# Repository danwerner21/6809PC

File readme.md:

# 6809PC
The 6809PC is a 6809 ATX format board with 512K RAM, 4K ROM, with a flexible programmable MMU, battery backed up RTC, 6551 UART, and 6 ISAish slots.  This computer will run the fantastic CUBIX operating system by Dave Dunfield.  

See this repo (https://github.com/danwerner21/CUBIX09) for ROM image and operating system.

## BUGS
I have not built the 1.31 version, but it contains fixes for the only bug found in the 1.30 version which was in the ATX power switch circuit. The ICs in that circuit were not powered by standby power, they were powered by +5 which made them non-functional.  There are no known remaining bugs in the 1.31 board.

### Jumper Settings
J1,J2,J5,J7,J9,J13 - ISA SLOT IRQ Selection
J11 - TTL Serial Port Connection
J12 - TTL Console Power

K1 - ROM BANK Selection (2-3 high bank, 1-2 Low Bank)
K2 - MMU Selection (1-2 Disable on int, 3-4 Clear Task register on int)

JP1 - Reset Swithc Connection
JP3 - CTS Pull Up Enable

P12 - Power Switch Connection
P15 - CPU Speed Selection
P18 - Serial Port Connection

### Building the system

### Default Memory Map
            $0000-$E000 - RAM
            $E000-$EFFF - Memory Mapped IO
            $F000-$FFFF - ROM

### Bill Of Materials
Reference|Value|Qty|Field1|Description
---------|-----|---|------|-----------
C1-C4,C17|22 uF|5||Polarized capacitor
C5-C16,C18-C27,C29-C33,C36-C54,C56,C58,C62|0.1 uF|49||Unpolarized capacitor
C28|1uF|1||Polarized capacitor
C35|10uF|1||Polarized capacitor
C57|0.01 uF|1||Unpolarized capacitor
C59,C60|15pf|2||Unpolarized capacitor
C61,C63-C66|1.0 uF|5||Polarized capacitor
D1,D2|1N4148|2||Diode
D3,D4|D|2||Diode
J1,J2,J5,J7,J9,J13|IRQ Selection|6||Generic connector, double row, 02x06, odd/even pin numbering scheme (row 1 odd numbers, row 2 even numbers), script generated (kicad-library-utils/schlib/autogen/connector/)
J3,J4,J6,J8,J10,J14|Bus_ISA_8bit|6||8-bit ISA-PC bus connector
J11|TTL SERIAL CONSOLE|1||Generic connector, single row, 01x06, script generated (kicad-library-utils/schlib/autogen/connector/)
J12|TTL CONSOLE PWR|1||Generic connector, single row, 01x02, script generated (kicad-library-utils/schlib/autogen/connector/)
JP1,JP3|JUMPER|2||-- mixed values --
K1|ROM SELECT|1||Generic connector, single row, 01x03, script generated (kicad-library-utils/schlib/autogen/connector/)
K2|MMU-INTA|1||Generic connector, single row, 01x03, script generated (kicad-library-utils/schlib/autogen/connector/)
P1|SHADOW ADDR|1||Generic connector, double row, 02x04, odd/even pin numbering scheme (row 1 odd numbers, row 2 even numbers), script generated (kicad-library-utils/schlib/autogen/connector/)
P11|CONN_10X2|1||Generic connector, double row, 02x10, odd/even pin numbering scheme (row 1 odd numbers, row 2 even numbers), script generated (kicad-library-utils/schlib/autogen/connector/)
P12|POWER_SW|1||Generic connector, single row, 01x02, script generated (kicad-library-utils/schlib/autogen/connector/)
P13|14.31818 MHz CLK|1||
P14|16.000Mhz|1||
P15|CPU CLOCK SPEED|1||Generic connector, double row, 02x04, odd/even pin numbering scheme (row 1 odd numbers, row 2 even numbers), script generated (kicad-library-utils/schlib/autogen/connector/)
P16|CONN_4|1||Generic connector, single row, 01x04, script generated (kicad-library-utils/schlib/autogen/connector/)
P17|1.8432 MHz CLK|1||
P18|SERIAL|1||Generic connector, double row, 02x05, odd/even pin numbering scheme (row 1 odd numbers, row 2 even numbers), script generated (kicad-library-utils/schlib/autogen/connector/)
R1,R3|10k|2||Resistor
R2|470|1||Resistor
R4,R7,R26|4.7K|3||Resistor
R5,R6,R8|1000|3||Resistor
RR1|2200|1||9 resistor network, star topology, bussed resistors, small symbol
RR2|22K|1||9 resistor network, star topology, bussed resistors, small symbol
SW1|POWER|1||Push button switch, generic, two pins
SW2|RESET|1||Push button switch, generic, two pins
U1|74LS04|1||Hex Inverter
U2,U34,U36,U39,U45,U46|74LS244|6||Octal Buffer and Line Driver With 3-State Output, active-low enables, non-inverting outputs
U3|74LS682|1||
U4|74LS86|1||Quad 2-input XOR
U5|74LS02|1||quad 2-input NOR gate
U6,U21|74LS00|2||quad 2-input NAND gate
U7,U10,U16|74LS32|3||Quad 2-input OR
U8|SRAM_512K|1||512K x 8 Low Power CMOS RAM, DIP-32
U9,U15|74LS08|2||Quad And2
U11|27C256|1||OTP EPROM 256 KiBit
U12,U22|74LS74|2||Dual D Flip-flop, Set & Reset
U17|74LS14|1||Hex inverter schmitt trigger
U18|74LS06|1||Inverter Open Collect
U19|74HCT14|1||Hex inverter schmitt trigger
U23|74LS688|1||8-bit magnitude comparator
U24,U42|74LS138|2||Decoder 3 to 8 active low outputs
U25-U28,U32,U41|74LS245|6||Octal BUS Transceivers, 3-State outputs
U29|DS1233|1||
U30|74LS163|1||Synchronous 4-bit programmable binary Counter
U31|74LS240|1||Octal Buffer and Line Driver With 3-State Output, active-low enables, inverting outputs
U33|MC68B09|1||8-Bit Microprocessing unit 2.0MHz, DIP-40
U35|74LS174|1||Hex D-type Flip-Flop, reset
U37|74LS157|1||Quad 2 to 1 line Multiplexer
U38|74LS374|1||8-bit Register, 3-state outputs
U40|SRAM-32K|1||256K (32K x 8) Static RAM, 70ns, DIP-28
U43,U44|74LS257|2||Quad 2 to 1 Multiplexer
U47|M6242|1||M6242
U48|G65SC51P|1||CMOS Asynchronous Communication Interface Adapter (ACIA), Serial UART, DIP-28
U49|MAX232|1||Dual RS232 driver/receiver, 5V supply, 120kb/s, 0C-70C
X1|RTC_OSC|1|32.768 KHz|Two pin crystal

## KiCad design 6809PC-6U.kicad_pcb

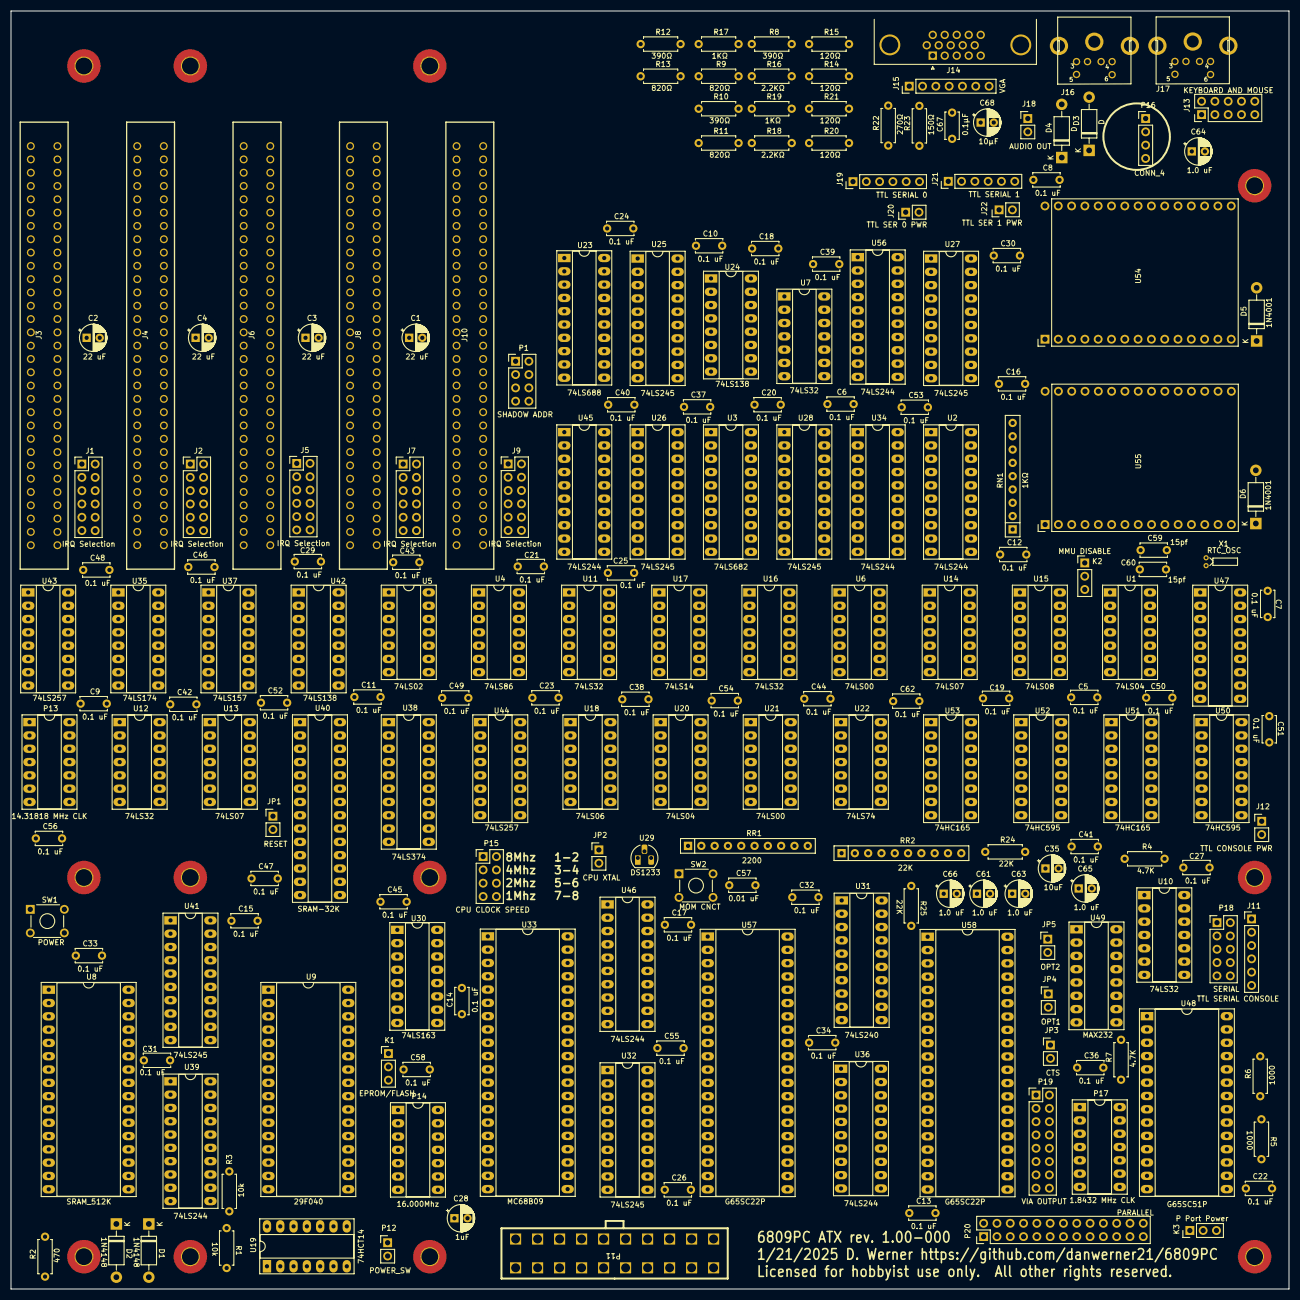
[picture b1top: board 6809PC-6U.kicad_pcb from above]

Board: 2 copper layers, 244.0 x 244.0 mm, 216 parts (0 on the bottom side), 371 nets, no tracks yet.

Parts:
C1, C2, C3, C4: 22 uF; STD_DDW_PCAP
C5, C6, C7, C8, C9, C10, C11, C12, C13, C14, C15, C16, C17, C18, C19, C20, C21, C22, C23, C24, C25, C26, C27, C29, C30, C31, C32, C33, C34, C36, C37, C38, C39, C40, C41, C42, C43, C44, C45, C46, C47, C48, C49, C50, C51, C52, C53, C54, C55, C56, C58, C62: 0.1 uF; STD_DDW_CAP
C28: 1uF; STD_DDW_PCAP
C35: 10uF; STD_DDW_PCAP
C57: 0.01 uF; STD_DDW_CAP
C59, C60: 15pf; STD_DDW_CAP
C61, C63, C64, C65, C66: 1.0 uF; STD_DDW_PCAP
C67: 0.1µF; STD_DDW_CAP
C68: 10µF; STD_DDW_PCAP
D1, D2: 1N4148; STD_DDW_DIODE
D3, D4: D; STD_DDW_DIODE
D5, D6: 1N4001; STD_DDW_DIODE
J1, J2, J5, J7, J9: IRQ Selection; STD_DDW_PINHEAD_V_2x06
J3, J4, J6, J8, J10: Bus_ISA_8bit; BUSPC_HOST
J11: TTL SERIAL CONSOLE; STD_DDW_PINHEAD_V_1x06
J12: TTL CONSOLE PWR; STD_DDW_PINHEAD_V_1x02
J13: KEYBOARD AND MOUSE; STD_DDW_PINHEAD_V_2x05
J14: VGA; STD_DDW_VGA
J15: VGA; STD_DDW_PINHEAD_V_1x07
J16: Keyboard; PS2_DIN
J17: Mouse; PS2_DIN
J18: AUDIO OUT; STD_DDW_PINHEAD_V_1x02
J19: TTL SERIAL 0; STD_DDW_PINHEAD_V_1x06
J20: TTL SER 0 PWR; STD_DDW_PINHEAD_V_1x02
J21: TTL SERIAL 1; STD_DDW_PINHEAD_V_1x06
J22: TTL SER 1 PWR; STD_DDW_PINHEAD_V_1x02
JP1: RESET; STD_DDW_PINHEAD_V_1x02
JP2: CPU XTAL; STD_DDW_PINHEAD_V_1x02
JP3: CTS; STD_DDW_PINHEAD_V_1x02
JP4: OPT1; STD_DDW_PINHEAD_V_1x02
JP5: OPT2; STD_DDW_PINHEAD_V_1x02
K1: EPROM/FLASH; STD_DDW_PINHEAD_V_1x03
K2: MMU DISABLE; STD_DDW_PINHEAD_V_1x03
K3: P Port Power; STD_DDW_PINHEAD_V_1x03
P1: SHADOW ADDR; STD_DDW_PINHEAD_V_2x04
P2, P3, P4, P5, P6, P7, P8, P9, P10, P21, P22, P23: CONN_1; MountingHole_3.2mm_M3_Pad_TopBottom
P11: CONN_10X2; ATXConnector
P12: POWER_SW; STD_DDW_PINHEAD_V_1x02
P13: 14.31818 MHz CLK; STD_DDW_DIP14
P14: 16.000Mhz; STD_DDW_DIP14
P15: CPU CLOCK SPEED; STD_DDW_PINHEAD_V_2x04
P16: CONN_4; STD_DDW_PINHEAD_V_1x04
P17: 1.8432 MHz CLK; STD_DDW_DIP14
P18: SERIAL; STD_DDW_PINHEAD_V_2x05
P19: VIA OUTPUT; STD_DDW_PINHEAD_V_2x08
P20: PARALLEL; STD_DDW_PINHEAD_V_2x13
R1, R3: 10k; STD_DDW_RESISTOR
R2: 470; STD_DDW_RESISTOR
R4, R7: 4.7K; STD_DDW_RESISTOR
R5, R6: 1000; STD_DDW_RESISTOR
R8, R10, R12: 390Ω; STD_DDW_RESISTOR
R9, R11, R13: 820Ω; STD_DDW_RESISTOR
R14, R15, R20, R21: 120Ω; STD_DDW_RESISTOR
R16, R18: 2.2KΩ; STD_DDW_RESISTOR
R17, R19: 1KΩ; STD_DDW_RESISTOR
R22: 270Ω; STD_DDW_RESISTOR
R23: 150Ω; STD_DDW_RESISTOR
R24, R25: 22K; STD_DDW_RESISTOR
RN1: 1KΩ; STD_DDW_SIP9
RR1: 2200; STD_DDW_SIP10
RR2: 22K; STD_DDW_SIP10
SW1: POWER; STD_DDW_TACTSW
SW2: MOM CNCT; STD_DDW_TACTSW
U1, U20: 74LS04; STD_DDW_DIP14
U2, U34, U36, U39, U45, U46, U56: 74LS244; STD_DDW_DIP20
U3: 74LS682; STD_DDW_DIP20
U4: 74LS86; STD_DDW_DIP14
U5: 74LS02; STD_DDW_DIP14
U6, U21: 74LS00; STD_DDW_DIP14
U7, U10, U11, U12, U16: 74LS32; STD_DDW_DIP14
U8: SRAM_512K; STD_DDW_DIP32
U9: 29F040; STD_DDW_DIP32
U13, U14: 74LS07; STD_DDW_DIP14
U15: 74LS08; STD_DDW_DIP14
U17: 74LS14; STD_DDW_DIP14
U18: 74LS06; STD_DDW_DIP14
U19: 74HCT14; STD_DDW_DIP14
U22: 74LS74; STD_DDW_DIP14
U23: 74LS688; STD_DDW_DIP20
U24, U42: 74LS138; STD_DDW_DIP16
U25, U26, U27, U28, U32, U41: 74LS245; STD_DDW_DIP20
U29: DS1233; STD_DDW_TO92
U30: 74LS163; STD_DDW_DIP16
U31: 74LS240; STD_DDW_DIP20
U33: MC68B09; STD_DDW_DIP40
U35: 74LS174; STD_DDW_DIP16
U37: 74LS157; STD_DDW_DIP16
U38: 74LS374; STD_DDW_DIP20
U40: SRAM-32K; STD_DDW_DIP28_SKINNY
U43, U44: 74LS257; STD_DDW_DIP16
U47: STD_DDW_DIP18
U48: G65SC51P; STD_DDW_DIP28
U49: MAX232; STD_DDW_DIP16
U50, U52: 74HC595; STD_DDW_DIP16
U51, U53: 74HC165; STD_DDW_DIP16
U54, U55: ESP32_MODULE; ESP32_Module
U57, U58: G65SC22P; STD_DDW_DIP40
X1: RTC_OSC; DDW_STD_RTCCRYSTAL

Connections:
5VSB: D1.1 (K), D2.1 (K), P11.17, R1.1, R3.2, U19.9, U19.11, U19.13, U22.1 (~R)
+3V3: C8.1, C12.1, C16.1, C20.1, C24.1, P11.1, P11.2, P11.3, R16.2, R17.2, R18.2, R19.2, RN1.1 (common)
+12V: J3.9 (+12V), J4.9 (+12V), J6.9 (+12V), J8.9 (+12V), J10.9 (+12V), P11.19
-5V: J3.5 (-5V), J4.5 (-5V), J6.5 (-5V), J8.5 (-5V), J10.5 (-5V), P11.16
-12V: J3.7 (-12V), J4.7 (-12V), J6.7 (-12V), J8.7 (-12V), J10.7 (-12V), P11.4
/ACIA/ACIA_CLK: P17.8, P17.9, P17.10, P17.11, U48.6 (XTAL1)
/ACIA/CTS: JP3.2 (B), P18.6, U49.13 (R1IN)
/ACIA/CTS_TTL: U48.9 (~CTS), U49.12 (R1OUT)
/ACIA/DCD: R6.2, U48.16 (~DCD)
/ACIA/DSR: R5.2, U48.17 (~DSR)
/ACIA/DTR: R7.2, U48.11 (~DTR)
/ACIA/RTS: P18.4, U49.14 (T1OUT)
/ACIA/RTS_TTL: U48.8 (~RTS), U49.11 (T1IN)
/ACIA/RXD: P18.3, U49.8 (R2IN)
/ACIA/RXD_TTL: J11.4, U48.12 (RxD), U49.9 (R2OUT)
/ACIA/TXD: P18.5, U49.7 (T2OUT)
/ACIA/TXD_TTL: J11.5, U48.10 (TxD), U49.10 (T2IN)
/CPU 6809/1MHZ: P15.7, U30.11 (Q3)
/CPU 6809/2MHZ: P15.5, U30.12 (Q2)
/CPU 6809/4MHZ: P15.3, U30.13 (Q1)
/CPU 6809/8MHZ: P15.1, U30.14 (Q0)
/CPU 6809//INTA: K2.2, U21.3
/MMU four/MMU-ENABLE: U22.9 (Q), U36.2 (I0a), U37.1 (S), U43.1 (S), U44.1 (S)
/MMU four//MMU-ENB-WR: U22.11 (C), U42.13 (O2)
/MMU four//MMU-MAP-RD: U10.11, U15.1
/MMU four//MMU-MAP-WR: U10.8, U40.27 (~WE)
/MMU four//MMU-TASK-RD: U36.1 (OEa), U36.4 (I1a), U36.19 (OEb), U42.11 (O4)
/MMU four//MMU-TASK-SETUP-WR: U38.11 (Cp), U42.14 (O1)
/MMU four//MMU-TASK-WR: U35.9 (Cp), U42.15 (O0)
/MMU four//OE: U15.3, U40.22 (~OE)
/Memory Map/SHADOW-ROM: U5.10, U5.11
/Memory Map//SHADOW: U3.19 (~P=Q), U5.5, U5.9, U6.2
/VIAS/CA1: P19.3, U57.40 (CA1)
/VIAS/CA2: P19.5, U57.39 (CA2)
/VIAS/CB1: P19.7, U57.18 (CB1)
/VIAS/CB2: P19.9, U57.19 (CB2)
/VIAS/CC1: P19.11, U58.40 (CA1)
/VIAS/CC2: P19.13, U58.39 (CA2)
/VIAS/PA0: P20.2, U57.2 (PA0)
/VIAS/PA1: P20.4, U57.3 (PA1)
/VIAS/PA2: P20.6, U57.4 (PA2)
/VIAS/PA3: P20.8, U57.5 (PA3)
/VIAS/PA4: P20.10, U57.6 (PA4)
/VIAS/PA5: P20.12, U57.7 (PA5)
/VIAS/PA6: P20.14, U57.8 (PA6)
/VIAS/PA7: P20.16, U57.9 (PA7)
/VIAS/PB0: P20.18, U57.10 (PB0)
/VIAS/PB1: P20.20, U57.11 (PB1)
/VIAS/PB2: P20.22, U57.12 (PB2)
/VIAS/PB3: P20.24, U57.13 (PB3)
/VIAS/PB4: P20.23, U57.14 (PB4)
/VIAS/PB5: P20.21, U57.15 (PB5)
/VIAS/PB6: P20.19, U57.16 (PB6)
/VIAS/PB7: P20.17, U57.17 (PB7)
/VIAS/PC0: P20.1, U58.2 (PA0)
/VIAS/PC1: P20.3, U58.3 (PA1)
/VIAS/PC2: P20.5, U58.4 (PA2)
/VIAS/PC3: P20.7, U58.5 (PA3)
/VIAS/PC4: P20.9, U58.6 (PA4)
/VIAS/PC5: P20.11, U58.7 (PA5)
/VIAS/PC6: P20.13, U58.8 (PA6)
/VIAS/PC7: P20.15, U58.9 (PA7)
/VIAS/PPWR: K3.2, P20.25
AUDIO: R22.1, U54.8 (GPIO25)
BUSAK: U4.9, U17.4, U32.19 (CE), U34.1 (OEa), U43.15 (OE), U44.15 (OE), U45.19 (OEb), U46.1 (OEa), U46.19 (OEb)
BUSALE: J3.28 (ALE), J4.28 (ALE), J6.28 (ALE), J8.28 (ALE), J10.28 (ALE), U17.2, U47.3 (ALE)
BUSCLK: J3.30 (OSC), J4.30 (OSC), J6.30 (OSC), J8.30 (OSC), J10.30 (OSC), P13.8, P13.9, P13.10, P13.11
B_A0: J3.62 (BA00), J4.62 (BA00), J6.62 (BA00), J8.62 (BA00), J10.62 (BA00), U26.18 (B0)
B_A1: J3.61 (BA01), J4.61 (BA01), J6.61 (BA01), J8.61 (BA01), J10.61 (BA01), U26.17 (B1)
B_A2: J3.60 (BA02), J4.60 (BA02), J6.60 (BA02), J8.60 (BA02), J10.60 (BA02), U26.16 (B2)
B_A3: J3.59 (BA03), J4.59 (BA03), J6.59 (BA03), J8.59 (BA03), J10.59 (BA03), U26.15 (B3)
B_A4: J3.58 (BA04), J4.58 (BA04), J6.58 (BA04), J8.58 (BA04), J10.58 (BA04), U26.14 (B4)
B_A5: J3.57 (BA05), J4.57 (BA05), J6.57 (BA05), J8.57 (BA05), J10.57 (BA05), U26.13 (B5)
B_A6: J3.56 (BA06), J4.56 (BA06), J6.56 (BA06), J8.56 (BA06), J10.56 (BA06), U26.12 (B6)
B_A7: J3.55 (BA07), J4.55 (BA07), J6.55 (BA07), J8.55 (BA07), J10.55 (BA07), U26.11 (B7)
B_A8: J3.54 (BA08), J4.54 (BA08), J6.54 (BA08), J8.54 (BA08), J10.54 (BA08), U27.18 (B0)
B_A9: J3.53 (BA09), J4.53 (BA09), J6.53 (BA09), J8.53 (BA09), J10.53 (BA09), U27.17 (B1)
B_A10: J3.52 (BA10), J4.52 (BA10), J6.52 (BA10), J8.52 (BA10), J10.52 (BA10), U27.16 (B2)
B_A11: J3.51 (BA11), J4.51 (BA11), J6.51 (BA11), J8.51 (BA11), J10.51 (BA11), U27.15 (B3)
B_A12: J3.50 (BA12), J4.50 (BA12), J6.50 (BA12), J8.50 (BA12), J10.50 (BA12), U27.14 (B4)
B_A13: J3.49 (BA13), J4.49 (BA13), J6.49 (BA13), J8.49 (BA13), J10.49 (BA13), U27.13 (B5)
B_A14: J3.48 (BA14), J4.48 (BA14), J6.48 (BA14), J8.48 (BA14), J10.48 (BA14), U27.12 (B6)
B_A15: J3.47 (BA15), J4.47 (BA15), J6.47 (BA15), J8.47 (BA15), J10.47 (BA15), U27.11 (B7)
B_A16: J3.46 (BA16), J4.46 (BA16), J6.46 (BA16), J8.46 (BA16), J10.46 (BA16), U28.18 (B0)
B_A17: J3.45 (BA17), J4.45 (BA17), J6.45 (BA17), J8.45 (BA17), J10.45 (BA17), U28.17 (B1)
B_A18: J3.44 (BA18), J4.44 (BA18), J6.44 (BA18), J8.44 (BA18), J10.44 (BA18), U28.16 (B2)
B_A19: J3.43 (BA19), J4.43 (BA19), J6.43 (BA19), J8.43 (BA19), J10.43 (BA19), U28.15 (B3)
B_D0: J3.40 (DB0), J4.40 (DB0), J6.40 (DB0), J8.40 (DB0), J10.40 (DB0), U25.18 (B0)
B_D1: J3.39 (DB1), J4.39 (DB1), J6.39 (DB1), J8.39 (DB1), J10.39 (DB1), U25.17 (B1)
B_D2: J3.38 (DB2), J4.38 (DB2), J6.38 (DB2), J8.38 (DB2), J10.38 (DB2), U25.16 (B2)
B_D3: J3.37 (DB3), J4.37 (DB3), J6.37 (DB3), J8.37 (DB3), J10.37 (DB3), U25.15 (B3)
B_D4: J3.36 (DB4), J4.36 (DB4), J6.36 (DB4), J8.36 (DB4), J10.36 (DB4), U25.14 (B4)
B_D5: J3.35 (DB5), J4.35 (DB5), J6.35 (DB5), J8.35 (DB5), J10.35 (DB5), U25.13 (B5)
B_D6: J3.34 (DB6), J4.34 (DB6), J6.34 (DB6), J8.34 (DB6), J10.34 (DB6), U25.12 (B6)
B_D7: J3.33 (DB7), J4.33 (DB7), J6.33 (DB7), J8.33 (DB7), J10.33 (DB7), U25.11 (B7)
B_INT: J1.1, J1.2, J1.3, J1.4, J1.5, J1.6, J2.1, J2.2, J2.3, J2.4, J2.5, J2.6, J5.1, J5.2, J5.3, J5.4, J5.5, J5.6, J7.1, J7.2, J7.3, J7.4, J7.5, J7.6, J9.1, J9.2, J9.3, J9.4, J9.5, J9.6, U18.13
B_/CLK: J3.20 (CLK), J4.20 (CLK), J6.20 (CLK), J8.20 (CLK), J10.20 (CLK), U31.18 (O0a)
B_/INT: RR1.2 (R1), U18.12, U31.6 (I2a)
B_/IORQ: U7.12, U16.4, U34.5 (O2b)
B_/MREQ: U16.1, U16.9, U28.12 (B6)
B_/NMI: J3.32 (IO), J4.32 (IO), J6.32 (IO), J8.32 (IO), J10.32 (IO), RR1.9 (R8), U31.4 (I1a)
B_/RD: U16.5, U16.10, U28.14 (B4)
B_/WR: U7.13, U16.2, U28.13 (B5)
CD1: JP4.2 (B), R24.2, U58.18 (CB1)
CD2: JP5.2 (B), R25.2, U58.19 (CB2)
CLK: P15.2, P15.4, P15.6, P15.8, U31.2 (I0a), U33.38 (EXTAL)
CPU_BA: U1.11, U33.6 (BA)
CPU_BS: RR2.10 (R9), U21.2, U33.5 (BS)
CPU_D0: U32.18 (B0), U33.31 (D0)
CPU_D1: U32.17 (B1), U33.30 (D1)
CPU_D2: U32.16 (B2), U33.29 (D2)
CPU_D3: U32.15 (B3), U33.28 (D3)
CPU_D4: U32.14 (B4), U33.27 (D4)
CPU_D5: U32.13 (B5), U33.26 (D5)
CPU_D6: U32.12 (B6), U33.25 (D6)
CPU_D7: U32.11 (B7), U33.24 (D7)
CPU_E: U5.2, U6.10, U33.34 (E), U34.17 (I3b), U45.6 (I2a)
CPU_Q: U5.3, U17.1, U33.35 (Q), U45.4 (I1a)
CPU_R/W: U1.1, U6.5, U33.32 (R/~W), U34.8 (I3a), U45.8 (I3a)
CPU_/RD: U6.6, U10.13, U12.10, U12.13, U16.13, U34.4 (I1a), U47.8 (RD)
CPU_/WR: U6.8, U10.9, U12.2, U12.5, U34.6 (I2a), U47.10 (WR)
E: U6.4, U34.3 (O3b), U42.6 (E3), U45.14 (O2a), U48.27 (ϕ2), U57.25 (ϕ2), U58.25 (ϕ2)
ESP0_BUSY: U54.11 (GPIO14), U56.4 (I1a)
ESP0_IN: RN1.7 (R6), U14.12, U54.22 (GPIO17)
ESP0_INCLK: U53.2 (CP), U54.10 (GPIO27)
ESP0_OUT: U52.14 (SER), U54.21 (GPIO16)
ESP0_OUTCLK: U52.11 (SRCLK), U52.12 (RCLK), U54.9 (GPIO26)
ESP0_RDYO: U54.12 (GPIO12), U56.2 (I0a)
ESP0_SEL: U11.6, U12.1, U12.9
ESP0_SPAREO: U54.19 (GPIO2), U56.6 (I2a)
ESP1_BUSY: U55.24 (GPIO18), U56.11 (I0b)
ESP1_IN: RN1.2 (R1), U14.10, U55.22 (GPIO17)
ESP1_INCLK: U51.2 (CP), U55.25 (GPIO19)
ESP1_OUT: U50.14 (SER), U55.21 (GPIO16)
ESP1_OUTCLK: U50.11 (SRCLK), U50.12 (RCLK), U55.26 (GPIO21)
ESP1_RDYO: U55.23 (GPIO5), U56.8 (I3a)
ESP1_SEL: U11.8, U12.4, U12.12
ESPSTAT_SEL: U11.11, U16.12
GND: C1.2, C2.2, C3.2, C4.2, C5.2, C6.2, C7.2, C8.2, C9.2, C10.2, C11.2, C12.2, C13.2, C14.2, C15.2, C16.2, C17.2, C18.2, C19.2, C20.2, C21.2, C22.2, C23.2, C24.2, C25.2, C26.2, C27.2, C28.2, C29.2, C30.2, C31.2, C32.2, C33.2, C34.2, C35.2, C36.2, C37.2, C38.2, C39.2, C40.2, C41.2, C42.2, C43.2, C44.2, C45.2, C46.2, C47.2, C48.2, C49.2, C50.2, C51.2, C52.2, C53.2, C54.2, C55.2, C56.2, C57.2, C58.2, C62.2, C64.2, C65.1, C67.2, J3.1 (GND), J3.10 (GND), J3.31 (GND), J4.1 (GND), J4.10 (GND), J4.31 (GND), J6.1 (GND), J6.10 (GND), J6.31 (GND), J8.1 (GND), J8.10 (GND), J8.31 (GND), J10.1 (GND), J10.10 (GND), J10.31 (GND), J11.1, J13.1, J13.3, J13.8, J13.10, J14.0, J14.5, J14.6, J14.7, J14.8, J14.10, J15.7, J16.3, J17.3, J18.2, J19.1, J21.1, JP1.2, JP2.1 (A), JP4.1 (A), JP5.1 (A), K3.1, P1.1, P1.3, P1.5, P1.7, P2.1, P3.1, P4.1, P5.1, P6.1, P7.1, P8.1, P9.1, P10.1, P11.5, P11.6, P11.9, P11.10, P11.12, P11.13, P11.14, P12.1, P13.4, P13.5, P13.6, P13.7, P14.4, P14.5, P14.6, P14.7, P16.2, P16.3, P16.4, P17.4, P17.5, P17.6, P17.7, P18.9, P19.15, P20.26, P21.1, P22.1, P23.1, R5.1, R6.1, R23.2, SW1.1, SW2.1, U1.7 (GND), U2.10 (GND), U2.17 (I3b), U3.10 (GND), U3.17 (P7), U3.18 (Q7), U4.7 (GND), U5.7 (GND), U6.7 (GND), U7.7 (GND), U8.16 (VSS), U9.16 (GND), U10.7 (GND), U11.7 (GND), U12.7 (GND), U13.7 (GND), U14.7 (GND), U15.7 (GND), U16.7 (GND), U17.7 (GND), U18.7 (GND), U19.7 (GND), U20.7 (GND), U21.7 (GND), U22.7 (GND), U23.10 (GND), U24.16 (VCC), U25.10 (GND), U25.19 (CE), U26.10 (GND), U26.19 (CE), U27.10 (GND), U27.19 (CE), U28.10 (GND), U28.19 (CE), U29.1, U30.8 (GND), U31.1 (OEa), U31.10 (GND), U32.10 (GND), U33.1 (VSS), U34.10 (GND), U34.19 (OEb), U35.8 (GND), U36.10 (GND), U37.8 (GND), U37.15 (E), U38.10 (GND), U39.10 (GND), U40.14 (GND), U40.20 (~CS), U41.10 (GND), U42.16 (VCC), U43.8 (GND), U44.8 (GND), U45.1 (OEa), U45.10 (GND), U46.10 (GND), U47.9 (GND), U48.1 (VSS), U49.15 (GND), U50.8 (GND), U51.8 (GND), U51.15 (~CE), U52.8 (GND), U53.8 (GND), U53.15 (~CE), U54.14 (GND), U54.17 (GND), U55.14 (GND), U55.17 (GND), U56.10 (GND), U56.13 (I1b), U56.15 (I2b), U56.17 (I3b), U57.1 (VSS), U58.1 (VSS)
IOR: J3.14 (~IOR), J4.14 (~IOR), J6.14 (~IOR), J8.14 (~IOR), J10.14 (~IOR), U16.8
IOW: J3.13 (~IOW), J4.13 (~IOW), J6.13 (~IOW), J8.13 (~IOW), J10.13 (~IOW), U16.6
KBDCLK: R20.2, U54.7 (GPIO33)
KBDDAT: R21.2, U54.6 (GPIO32)
LA0: U33.8 (A0), U45.11 (I0b)
LA1: U33.9 (A1), U45.13 (I1b)
LA2: U33.10 (A2), U45.15 (I2b)
LA3: U33.11 (A3), U45.17 (I3b)
LA4: U33.12 (A4), U46.2 (I0a)
LA5: U33.13 (A5), U46.4 (I1a)
LA6: U33.14 (A6), U46.6 (I2a)
LA7: U33.15 (A7), U46.8 (I3a)
LA8: U33.16 (A8), U46.11 (I0b)
LA9: U33.17 (A9), U46.13 (I1b)
LA10: U33.18 (A10), U46.15 (I2b)
LA11: U33.19 (A11), U46.17 (I3b)
LA12: U33.20 (A12), U37.3 (I1a), U43.2 (I0a)
LA13: U33.21 (A13), U37.6 (I1b), U43.5 (I0b)
LA14: U33.22 (A14), U37.10 (I1c), U43.14 (I0c)
LA15: U33.23 (A15), U37.13 (I1d), U43.11 (I0d)
MRDY: RR2.3 (R2), U33.36 (MRDY)
MSECLK: R15.1, U55.7 (GPIO33)
MSEDAT: R14.1, U55.6 (GPIO32)
unnamed: C67.1, C68.1, R22.2, R23.1
unnamed: C28.1, D1.2 (A), R2.1, U19.3
unnamed: C35.1, D2.2 (A), R3.1, U19.1
unnamed: C59.1, C60.1, D3.1 (K), D4.1 (K), U47.18 (VCC)
unnamed: D4.2 (A), P16.1
unnamed: D5.1 (K), U54.15 (VIN)
unnamed: D6.1 (K), U55.15 (VIN)
unnamed: J1.8, J3.25 (IRQ3)
unnamed: J1.9, J3.24 (IRQ4)
unnamed: J1.10, J3.23 (IRQ5)
unnamed: J1.11, J3.22 (IRQ6)
unnamed: J1.12, J3.21 (IRQ7)
unnamed: J2.8, J4.25 (IRQ3)
unnamed: J2.9, J4.24 (IRQ4)
unnamed: J2.10, J4.23 (IRQ5)
unnamed: J2.11, J4.22 (IRQ6)
unnamed: J2.12, J4.21 (IRQ7)
unnamed: J5.8, J6.25 (IRQ3)
unnamed: J5.9, J6.24 (IRQ4)
unnamed: J5.10, J6.23 (IRQ5)
unnamed: J5.11, J6.22 (IRQ6)
unnamed: J5.12, J6.21 (IRQ7)
unnamed: J7.8, J8.25 (IRQ3)
unnamed: J7.9, J8.24 (IRQ4)
unnamed: J7.10, J8.23 (IRQ5)
unnamed: J7.11, J8.22 (IRQ6)
unnamed: J7.12, J8.21 (IRQ7)
unnamed: J9.8, J10.25 (IRQ3)
unnamed: J9.9, J10.24 (IRQ4)
unnamed: J9.10, J10.23 (IRQ5)
unnamed: J9.11, J10.22 (IRQ6)
unnamed: J9.12, J10.21 (IRQ7)
unnamed: J11.3, J12.2
unnamed: J13.2, J16.5, R19.1, R20.1
unnamed: J13.4, J16.1, R18.1, R21.1
unnamed: J13.7, J17.1, R14.2, R16.1
unnamed: J13.9, J17.5, R15.2, R17.1
unnamed: J14.1, J15.3, R8.2, R9.2
unnamed: J14.2, J15.4, R10.2, R11.2
unnamed: J14.3, J15.5, R12.2, R13.2
unnamed: C68.2, J18.1
unnamed: J19.3, J20.2
unnamed: J21.3, J22.2
unnamed: JP2.2 (B), U33.39 (XTAL)
unnamed: JP3.1 (A), R4.2
unnamed: P12.2, R1.2, R2.2, SW1.2
unnamed: U1.6, U4.1
unnamed: U1.8, U5.8
unnamed: U1.12, U21.5
unnamed: U4.3, U6.1
unnamed: U4.6, U5.12
unnamed: U5.13, U7.1
unnamed: U6.3, U7.5
unnamed: U7.6, U8.22 (CE#)
unnamed: U7.3, U9.22 (CE)
unnamed: U10.1, U10.4, U20.2
unnamed: U10.3, U11.10
unnamed: U10.5, U20.4
unnamed: U10.6, U11.13
unnamed: U11.3, U11.4
unnamed: U19.2, U19.5
unnamed: U7.9, U21.6
unnamed: U4.8, U21.9
unnamed: U6.11, U21.10
unnamed: U19.4, U22.3 (C)
unnamed: U22.2 (D), U22.6 (~Q)
unnamed: U19.6, U22.4 (~S)
unnamed: U15.6, U22.13 (~R)
unnamed: U23.19 (P=R), U24.4 (E1), U24.5 (E2)
unnamed: U21.8, U25.1 (A->B)
unnamed: P14.8, P14.9, P14.10, P14.11, U30.2 (CP)
unnamed: U18.9, U31.16 (O1a)
unnamed: U18.11, U31.14 (O2a)
unnamed: U5.1, U34.2 (I0a)
unnamed: U35.2 (Q0), U36.17 (I3b), U39.2 (I0a)
unnamed: U35.5 (Q1), U36.15 (I2b), U39.4 (I1a)
unnamed: U35.7 (Q2), U36.13 (I1b), U39.6 (I2a)
unnamed: U35.10 (Q3), U36.11 (I0b), U39.8 (I3a)
unnamed: U35.12 (Q4), U36.8 (I3a), U39.11 (I0b)
unnamed: U35.15 (Q5), U36.6 (I2a), U39.13 (I1b)
unnamed: U15.8, U35.1 (~Mr)
unnamed: U37.4 (Za), U40.10 (A0)
unnamed: U37.7 (Zb), U40.9 (A1)
unnamed: U37.9 (Zc), U40.8 (A2)
unnamed: U37.12 (Zd), U40.7 (A3)
unnamed: U38.2 (O0), U39.18 (O0a), U40.6 (A4)
unnamed: U38.5 (O1), U39.16 (O1a), U40.5 (A5)
unnamed: U38.6 (O2), U39.14 (O2a), U40.4 (A6)
unnamed: U38.9 (O3), U39.12 (O3a), U40.3 (A7)
unnamed: U38.12 (O4), U39.9 (O0b), U40.25 (A8)
unnamed: U38.15 (O5), U39.7 (O1b), U40.24 (A9)
unnamed: U1.4, U39.1 (OEa), U39.19 (OEb)
unnamed: U40.11 (Q0), U41.2 (A0), U43.3 (I1a)
unnamed: U40.12 (Q1), U41.3 (A1), U43.6 (I1b)
unnamed: U40.13 (Q2), U41.4 (A2), U43.13 (I1c)
unnamed: U40.15 (Q3), U41.5 (A3), U43.10 (I1d)
unnamed: U40.16 (Q4), U41.6 (A4), U44.3 (I1a)
unnamed: U40.17 (Q5), U41.7 (A5), U44.6 (I1b)
unnamed: U40.18 (Q6), U41.8 (A6), U44.13 (I1c)
unnamed: U40.19 (Q7), U41.9 (A7), U44.10 (I1d)
unnamed: C59.2, U47.17 (XT1), X1.2
unnamed: C60.2, U47.16 (XT), X1.1
unnamed: C61.1, U49.1 (C1+)
unnamed: C61.2, U49.3 (C1-)
unnamed: C63.1, U49.4 (C2+)
unnamed: C63.2, U49.5 (C2-)
unnamed: C66.1, U49.2 (VS+)
unnamed: C65.2, U49.6 (VS-)
unnamed: U14.11, U51.9 (Q7)
unnamed: U14.13, U53.9 (Q7)
PD0: P19.2, U58.10 (PB0)
PD1: P19.4, U58.11 (PB1)
PD2: P19.6, U58.12 (PB2)
PD3: P19.8, U58.13 (PB3)
PD4: P19.10, U58.14 (PB4)
PD5: P19.12, U58.15 (PB5)
PD6: P19.14, U58.16 (PB6)
PD7: P19.16, U58.17 (PB7)
PG: P11.15, RR1.6 (R5)
PULLUP1: RR1.3 (R2), U47.15 (CS1)
PULLUP2: K1.2, RR1.4 (R3), U9.31 (PGM)
PULLUP3: RR1.5 (R4), U52.10 (~SRCLR)
PULLUP4: RR1.7 (R6), U50.10 (~SRCLR)
PWR_ON: P11.8, U22.5 (Q)
RX: J19.4, U54.27 (GPIO3)
RX1: J21.4, U55.27 (GPIO3)
R/W: U4.10, U32.1 (A->B), U34.12 (O3a), U41.1 (A->B), U42.3 (A2), U45.12 (O3a), U48.28 (R/~W), U57.22 (R/~W), U58.22 (R/~W)
SHADOW-IO: U5.4, U21.4, U23.2 (P0)
SMEMR: J3.12 (~SMEMR), J4.12 (~SMEMR), J6.12 (~SMEMR), J8.12 (~SMEMR), J10.12 (~SMEMR), U16.3
SMEMW: J3.11 (~SMEMW), J4.11 (~SMEMW), J6.11 (~SMEMW), J8.11 (~SMEMW), J10.11 (~SMEMW), U7.11
TX: J19.5, U54.28 (GPIO1)
TX1: J21.5, U55.28 (GPIO1)
VCC: C1.1, C2.1, C3.1, C4.1, C5.1, C6.1, C7.1, C9.1, C10.1, C11.1, C13.1, C14.1, C15.1, C17.1, C18.1, C19.1, C21.1, C22.1, C23.1, C25.1, C26.1, C27.1, C29.1, C30.1, C31.1, C32.1, C33.1, C34.1, C36.1, C37.1, C38.1, C39.1, C40.1, C41.1, C42.1, C43.1, C44.1, C45.1, C46.1, C47.1, C48.1, C49.1, C50.1, C51.1, C52.1, C53.1, C54.1, C55.1, C56.1, C58.1, C62.1, C64.1, C66.2, D3.2 (A), D5.2 (A), D6.2 (A), J3.3 (VCC), J3.29 (VCC), J4.3 (VCC), J4.29 (VCC), J6.3 (VCC), J6.29 (VCC), J8.3 (VCC), J8.29 (VCC), J10.3 (VCC), J10.29 (VCC), J12.1, J13.5, J13.6, J15.6, J16.4, J17.4, J20.1, J22.1, K3.3, P11.7, P11.11, P11.18, P11.20, P13.14, P14.14, P17.14, P19.1, R4.1, R7.1, R24.1, R25.1, RR1.1 (common), RR2.1 (common), U1.14 (VCC), U2.11 (I0b), U2.13 (I1b), U2.15 (I2b), U2.20 (VCC), U3.12 (Q4), U3.14 (Q5), U3.16 (Q6), U3.20 (VCC), U4.14 (VCC), U5.14 (VCC), U6.14 (VCC), U7.14 (VCC), U8.32 (VCC), U9.32 (VCC), U10.14 (VCC), U11.14 (VCC), U12.14 (VCC), U13.14 (VCC), U14.14 (VCC), U15.14 (VCC), U16.14 (VCC), U17.14 (VCC), U18.14 (VCC), U19.14 (VCC), U20.14 (VCC), U21.14 (VCC), U22.10 (~S), U22.14 (VCC), U23.3 (R0), U23.4 (P1), U23.5 (R1), U23.7 (R2), U23.9 (R3), U23.12 (R4), U23.14 (R5), U23.16 (R6), U23.17 (P7), U23.18 (R7), U23.20 (VCC), U24.6 (E3), U24.8 (GND), U25.20 (VCC), U26.20 (VCC), U27.20 (VCC), U28.20 (VCC), U29.3, U30.1 (~MR), U30.3 (D0), U30.4 (D1), U30.5 (D2), U30.6 (D3), U30.7 (CEP), U30.9 (~PE), U30.10 (CET), U30.16 (VCC), U31.20 (VCC), U32.20 (VCC), U33.7 (VCC), U34.20 (VCC), U35.16 (VCC), U36.20 (VCC), U37.16 (VCC), U38.20 (VCC), U39.20 (VCC), U40.1 (A14), U40.2 (A12), U40.21 (A10), U40.23 (A11), U40.26 (A13), U40.28 (VCC), U41.20 (VCC), U42.8 (GND), U43.16 (VCC), U44.16 (VCC), U45.20 (VCC), U46.20 (VCC), U48.15 (VCC), U49.16 (VCC), U50.16 (VCC), U51.16 (VCC), U52.16 (VCC), U53.16 (VCC), U56.20 (VCC), U57.20 (VCC), U57.24 (CS1), U58.20 (VCC), U58.24 (CS1)
VGA_B0: R13.1, U54.20 (GPIO4)
VGA_B1: R12.1, U54.23 (GPIO5)
VGA_G0: R11.1, U54.24 (GPIO18)
VGA_G1: R10.1, U54.25 (GPIO19)
VGA_HSYNC: J14.13, J15.1, U54.30 (GPIO23)
VGA_R0: R9.1, U54.26 (GPIO21)
VGA_R1: R8.1, U54.29 (GPIO22)
VGA_VSYNC: J14.14, J15.2, U54.18 (GPIO15)
W/R: U1.2, U6.9
XM16: P1.8, U2.8 (I3a), U3.9 (Q3), U44.2 (I0a)
XM17: P1.6, U2.6 (I2a), U3.7 (Q2), U44.5 (I0b)
XM18: P1.4, U2.4 (I1a), U3.5 (Q1), U44.14 (I0c)
XM19: P1.2, U1.5, U2.2 (I0a), U3.3 (Q0), U4.5, U44.11 (I0d)
isa_iq_1: J2.7, J4.4 (IRQ2)
isa_iq_2: J5.7, J6.4 (IRQ2)
isa_iq_3: J7.7, J8.4 (IRQ2)
isa_iq_4: J9.7, J10.4 (IRQ2)
isa_iq_5: J1.7, J3.4 (IRQ2)
mA0: U8.12 (A0), U9.12 (A0), U11.2, U20.1, U26.2 (A0), U37.2 (I0a), U42.1 (A0), U45.9 (O0b), U47.4 (A0), U48.13 (RS0), U57.38 (RS0), U58.38 (RS0)
mA1: U8.11 (A1), U9.11 (A1), U10.2, U11.5, U20.3, U26.3 (A1), U37.5 (I0b), U42.2 (A1), U45.7 (O1b), U47.5 (A1), U48.14 (RS1), U57.37 (RS1), U58.37 (RS1)
mA2: U8.10 (A2), U9.10 (A2), U26.4 (A2), U37.11 (I0c), U45.5 (O2b), U47.6 (A2), U48.2 (CS1), U57.36 (RS2), U58.36 (RS2)
mA3: U8.9 (A3), U9.9 (A3), U26.5 (A3), U37.14 (I0d), U45.3 (O3b), U47.7 (A3), U57.35 (RS3), U58.35 (RS3)
mA4: U8.8 (A4), U9.8 (A4), U24.1 (A0), U26.6 (A4), U46.18 (O0a)
mA5: U8.7 (A5), U9.7 (A5), U24.2 (A1), U26.7 (A5), U46.16 (O1a)
mA6: U8.6 (A6), U9.6 (A6), U24.3 (A2), U26.8 (A6), U42.5 (E2), U46.14 (O2a)
mA7: U8.5 (A7), U9.5 (A7), U23.15 (P6), U26.9 (A7), U46.12 (O3a)
mA8: U8.27 (A8), U9.27 (A8), U23.13 (P5), U27.2 (A0), U46.9 (O0b)
mA9: U8.26 (A9), U9.26 (A9), U23.11 (P4), U27.3 (A1), U46.7 (O1b)
mA10: U8.23 (A10), U9.23 (A10), U23.8 (P3), U27.4 (A2), U46.5 (O2b)
mA11: U1.13, U8.25 (A11), U9.25 (A11), U23.6 (P2), U27.5 (A3), U46.3 (O3b)
mA12: U1.9, U5.6, U8.4 (A12), U9.4 (A12), U27.6 (A4), U43.4 (Za)
mA13: U3.15 (P6), U8.28 (A13), U9.28 (A13), U27.7 (A5), U43.7 (Zb)
mA14: U3.13 (P5), U8.3 (A14), U9.29 (A14), U27.8 (A6), U43.12 (Zc)
mA15: U3.11 (P4), U8.31 (A15), U9.3 (A15), U27.9 (A7), U43.9 (Zd)
mA16: U3.8 (P3), U8.2 (A16), U9.2 (A16), U28.2 (A0), U44.4 (Za)
mA17: U3.6 (P2), U8.30 (A17), U9.30 (A17), U28.3 (A1), U44.7 (Zb)
mA18: K1.3, U3.4 (P1), U8.1 (A18), U9.1 (A18), U28.4 (A2), U44.12 (Zc)
mA19: U3.2 (P0), U4.2, U4.4, U28.5 (A3), U44.9 (Zd)
mD0: U2.3 (O3b), U8.13 (DQ0), U9.13 (D0), U22.12 (D), U25.2 (A0), U32.2 (A0), U35.3 (D0), U36.3 (O3b), U38.3 (D0), U41.18 (B0), U47.14 (D0), U48.18 (D0), U50.15 (QA), U51.11 (D0), U52.15 (QA), U53.11 (D0), U56.18 (O0a), U57.33 (D0), U58.33 (D0)
mD1: U2.5 (O2b), U8.14 (DQ1), U9.14 (D1), U25.3 (A1), U32.3 (A1), U35.4 (D1), U36.5 (O2b), U38.4 (D1), U41.17 (B1), U47.13 (D1), U48.19 (D1), U50.1 (QB), U51.12 (D1), U52.1 (QB), U53.12 (D1), U56.16 (O1a), U57.32 (D1), U58.32 (D1)
mD2: U2.7 (O1b), U8.15 (DQ2), U9.15 (D2), U25.4 (A2), U32.4 (A2), U35.6 (D2), U36.7 (O1b), U38.7 (D2), U41.16 (B2), U47.12 (D2), U48.20 (D2), U50.2 (QC), U51.13 (D2), U52.2 (QC), U53.13 (D2), U56.14 (O2a), U57.31 (D2), U58.31 (D2)
mD3: U2.9 (O0b), U8.17 (DQ3), U9.17 (D3), U25.5 (A3), U32.5 (A3), U35.11 (D3), U36.9 (O0b), U38.8 (D3), U41.15 (B3), U47.11 (D3), U48.21 (D3), U50.3 (QD), U51.14 (D3), U52.3 (QD), U53.14 (D3), U56.12 (O3a), U57.30 (D3), U58.30 (D3)
mD4: U2.12 (O3a), U8.18 (DQ4), U9.18 (D4), U25.6 (A4), U32.6 (A4), U35.13 (D4), U36.12 (O3a), U38.13 (D4), U41.14 (B4), U48.22 (D4), U50.4 (QE), U51.3 (D4), U52.4 (QE), U53.3 (D4), U56.9 (O0b), U57.29 (D4), U58.29 (D4)
mD5: U2.14 (O2a), U8.19 (DQ5), U9.19 (D5), U25.7 (A5), U32.7 (A5), U35.14 (D5), U36.14 (O2a), U38.14 (D5), U41.13 (B5), U48.23 (D5), U50.5 (QF), U51.4 (D5), U52.5 (QF), U53.4 (D5), U56.7 (O1b), U57.28 (D5), U58.28 (D5)
mD6: U2.16 (O1a), U8.20 (DQ6), U9.20 (D6), U25.8 (A6), U32.8 (A6), U36.16 (O1a), U41.12 (B6), U48.24 (D6), U50.6 (QG), U51.5 (D6), U52.6 (QG), U53.5 (D6), U56.5 (O2b), U57.27 (D6), U58.27 (D6)
mD7: U2.18 (O0a), U8.21 (DQ7), U9.21 (D7), U25.9 (A7), U32.9 (A7), U36.18 (O0a), U41.11 (B7), U48.25 (D7), U50.7 (QH), U51.6 (D7), U52.7 (QH), U53.6 (D7), U56.3 (O3b), U57.26 (D7), U58.26 (D7)
/BUSAK: U1.10, U6.12, U17.3, U21.1, U26.1 (A->B), U27.1 (A->B), U28.1 (A->B)
/FIRQ: RR2.7 (R6), U33.4 (~FIRQ)
/HALT: RR2.2 (R1), U33.40 (~HALT)
/IORQ: U6.13, U7.8, U34.15 (I2b)
/IOSEL-0EF80: U24.15 (O0), U48.3 (~CS2)
/IOSEL-0EF90: U24.14 (O1), U47.2 (CS0)
/IOSEL-0EFA0: U24.13 (O2), U57.23 (~CS2)
/IOSEL-0EFB0: U24.12 (O3), U58.23 (~CS2)
/IOSEL-0EFC0: U11.1, U11.9, U11.12, U24.11 (O4)
/IOSEL-0EFD0: U1.3, U10.10, U10.12, U24.10 (O5), U38.1 (OE), U41.19 (CE)
/IOSEL-0EFE0: U24.9 (O6), U42.4 (E1)
/IRQ: RR2.6 (R5), U18.10, U33.3 (~IRQ), U48.26 (~IRQ), U57.21 (~IRQ), U58.21 (~IRQ)
/MMU-CLR-TASK-REG: K2.3, RR2.9 (R8), U15.10
/MMU-DISABLE: K2.1, RR2.8 (R7), U15.4
/MMU-IO-PREFIX-RD: U2.1 (OEa), U2.19 (OEb), U42.7 (O7)
/NMI: RR2.5 (R4), U18.8, U33.2 (~NMI)
/RD: U8.24 (OE#), U9.24 (OE), U28.6 (A4), U34.16 (O1a)
/RESET: C57.1, J3.2 (RESET), J4.2 (RESET), J6.2 (RESET), J8.2 (RESET), J10.2 (RESET), JP1.1, RR1.8 (R7), SW2.2, U13.1, U15.5, U15.9, U29.2, U33.37 (~RESET), U48.4 (~RES), U57.34 (~RES), U58.34 (~RES)
/VMA: U7.2, U7.4, U7.10, U15.2, U23.1 (G), U28.8 (A6), U34.18 (O0a)
/WR: K1.1, U8.29 (WE#), U28.7 (A5), U34.14 (O2a)
~ESP0_RD: RN1.4 (R3), U14.6, U52.13 (~OE), U54.13 (GPIO13)
~ESP0_WR: RN1.6 (R5), U14.2, U53.1 (~PL), U54.2 (GPIO36)
~ESP1_RD: RN1.3 (R2), U14.8, U50.13 (~OE), U55.29 (GPIO22)
~ESP1_WR: RN1.5 (R4), U14.4, U51.1 (~PL), U55.30 (GPIO23)
~ESP_RESET: RN1.8 (R7), U13.2, U54.1 (RESET), U55.1 (RESET)
~ESP_STAT: U16.11, U56.1 (OEa), U56.19 (OEb)
~PRE_ESP0_RD: U12.8, U14.5
~PRE_ESP0_WR: U12.3, U14.1
~PRE_ESP1_RD: U12.11, U14.9
~PRE_ESP1_WR: U12.6, U14.3

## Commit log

2025-01-21 Initial
2025-01-21 Schematic in progress
2025-01-22 PCB in progress
2025-03-01 V1.1
2025-05-18 6809PC work
2025-05-19 fix issue with ISA RW select lines
2025-06-02 fix bus issue
2025-06-09 debug work
2025-06-21 fix power supply switch circuit
2025-07-06 isa work
2025-07-13 update docs
